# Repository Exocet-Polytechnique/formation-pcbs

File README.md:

# Formation PCBs

Bienvenue à la formation d'Exocet sur la conception de circuits imprimés à l'aide du logiciel
KiCad! Les instructions sous forme écrite sont disponibles sur le
[wiki](https://github.com/Exocet-Polytechnique/formation-pcbs/wiki). Autrement, les quatre parties
de la formation sont dispensées en ligne sur Discord. Les enregistrements sont aussi disponibles à
la demande.

Pour suivre la formation, vous pouvez créer une nouvelle branche sur ce dépôt et la nommer avec
votre nom en minuscules. De cette manière, nous pourrons la visiter pour donner du feedback sur
votre projet.

# Licence

Les instructions sont disponibles publiquement sous la licence `CC0 1.0`, dont le texte est
[disponible ici](LICENSE). Les licences des projets KiCad sont à la discrétion de leurs
contributeurs respectifs. Ainsi, vous n'avez aucun droit sur les fichiers de projet à moins d'en
avoir l'accord explicite de la part du ou des contributeur(s) ayant travaillé dessus.

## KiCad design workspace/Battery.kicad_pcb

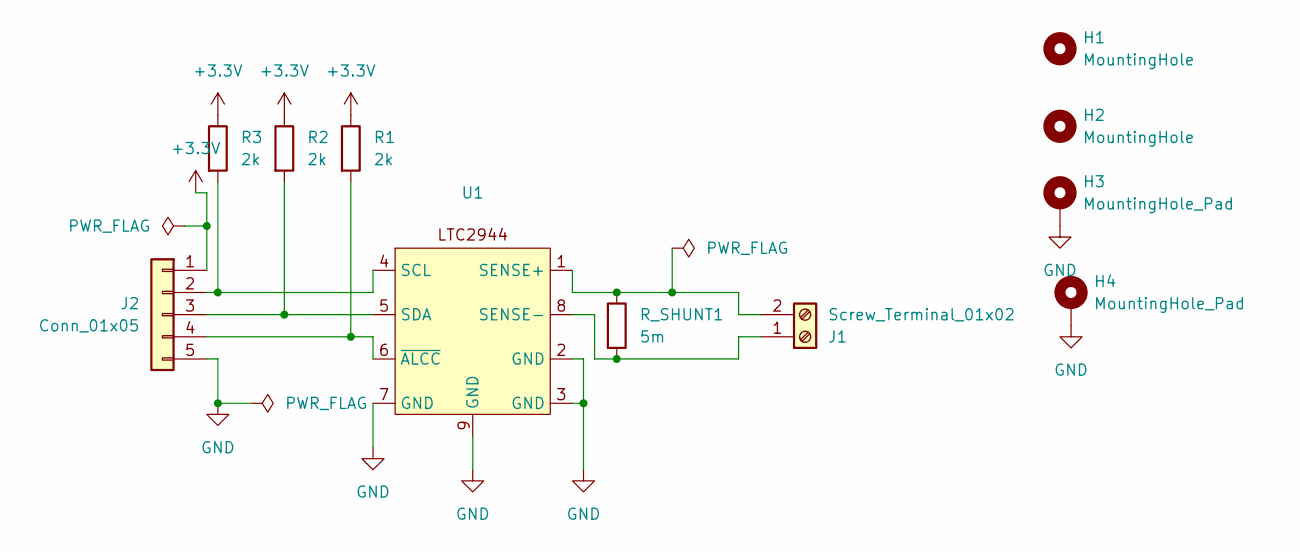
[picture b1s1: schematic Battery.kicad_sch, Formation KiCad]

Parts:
H1, H2: MountingHole; MountingHole_2.7mm
H3, H4: MountingHole_Pad; MountingHole_2.7mm_Pad
J1: Screw_Terminal_01x02; TerminalBlock_Phoenix_MKDS-1,5-2_1x02_P5.00mm_Horizontal
J2: Conn_01x05; JST_PH_S5B-PH-K_1x05_P2.00mm_Horizontal
R1, R2, R3: 2k; R_0603_1608Metric
R_SHUNT1: 5m; Milliohm_Shunt_2512
U1: DFN-8-1EP_3x3mm_P0.5mm_EP1.65x2.38mm_ThermalVias

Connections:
+3.3V: J2.1, R1.1, R2.1, R3.1
GND: H3.1, H4.1, J2.5, U1.2 (GND), U1.3 (GND), U1.7 (GND), U1.9 (GND)
unnamed: J1.1, R_SHUNT1.2, U1.8 (SENSE-)
unnamed: J1.2, R_SHUNT1.1, U1.1 (SENSE+)
unnamed: J2.2, R3.2, U1.4 (SCL)
unnamed: J2.3, R2.2, U1.5 (SDA)
unnamed: J2.4, R1.2, U1.6 (~ALCC)

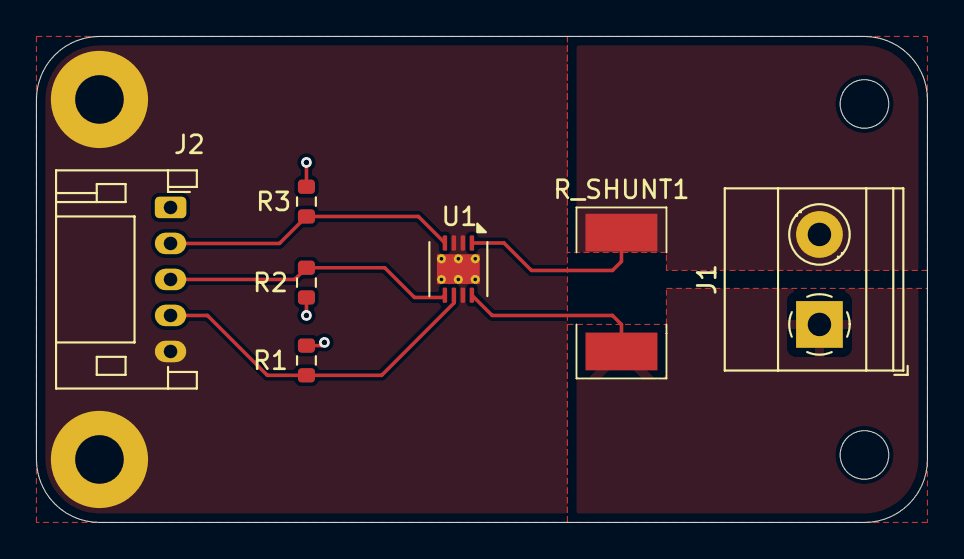
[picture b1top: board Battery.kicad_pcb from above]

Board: 2 copper layers, 49.5 x 27.0 mm, 11 parts (0 on the bottom side), 7 nets.

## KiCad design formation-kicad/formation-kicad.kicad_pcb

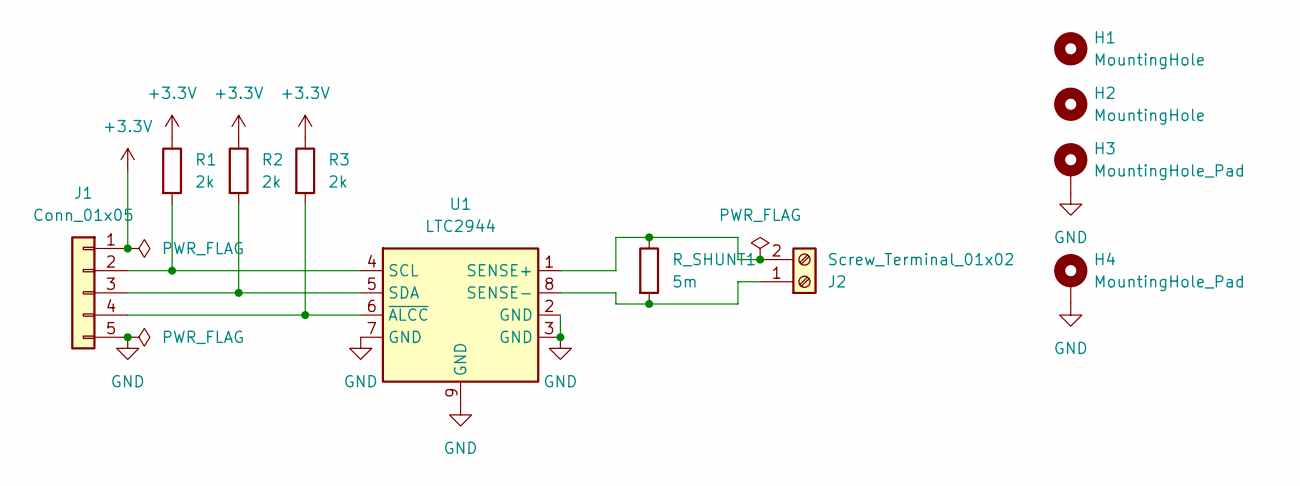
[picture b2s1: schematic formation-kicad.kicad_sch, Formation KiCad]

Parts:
H1, H2: MountingHole; MountingHole_2.7mm
H3, H4: MountingHole_Pad; MountingHole_2.7mm_M2.5_Pad
J1: Conn_01x05; JST_PH_S5B-PH-K_1x05_P2.00mm_Horizontal
J2: Screw_Terminal_01x02; TerminalBlock_Phoenix_MKDS-1,5-2_1x02_P5.00mm_Horizontal
R1, R2, R3: 2k; R_0603_1608Metric
R_SHUNT1: 5m; Milliohm_Shunt_2512
U1: LTC2944; DFN-8-1EP_3x3mm_P0.5mm_EP1.65x2.38mm_ThermalVias

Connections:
+3.3V: J1.1, R1.1, R2.1, R3.1
GND: H3.1, H4.1, J1.5, U1.2 (GND), U1.3 (GND), U1.7 (GND), U1.9 (GND)
unnamed: J1.2, R1.2, U1.4 (SCL)
unnamed: J1.3, R2.2, U1.5 (SDA)
unnamed: J1.4, R3.2, U1.6 (~ALCC)
unnamed: J2.1, R_SHUNT1.2, U1.8 (SENSE-)
unnamed: J2.2, R_SHUNT1.1, U1.1 (SENSE+)

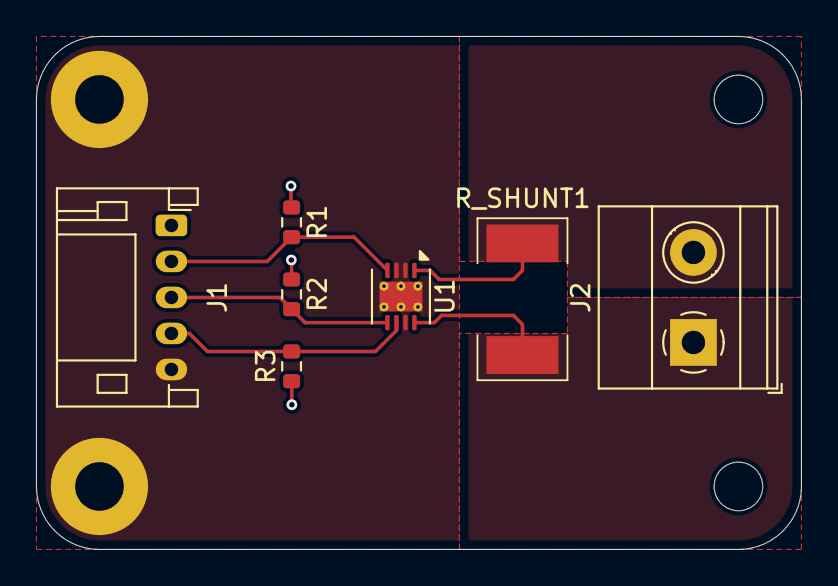
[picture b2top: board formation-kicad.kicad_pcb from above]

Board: 2 copper layers, 42.5 x 28.5 mm, 11 parts (0 on the bottom side), 7 nets.

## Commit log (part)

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2024-09-21 Accueil (README.md)
2024-09-25 Vocabulaire et Introduction
2024-09-26 Compléter l'introduction
2024-09-27 Correction
2024-09-27 Update Vocabulaire.md
    description via
2024-09-27 Update Vocabulaire.md
    correction description via
2024-09-27 Update Vocabulaire.md
    description plan (plane)
2024-09-27 Update Vocabulaire.md
    correction description plan (plane)
2024-09-27 Update Vocabulaire.md
    description empreinte
2024-09-29 Update Vocabulaire.md
    Ajouté quelques descriptions supplémentaires aux pièces et aux planes
2024-09-29 Add files via upload
    Ajout d'images pertinentes
2024-09-29 Rename image.png to Transistor.png
2024-09-29 Update 0. Introduction.md
    me souviens plus ce que j'ai fait
2024-09-29 Update 1. Introduction.md
    Ajout de certaines étapes pertinentes à la réalisation d'un PCB
2024-09-29 Update Vocabulaire.md
    Images
2024-09-29 ajout images
    duh
2024-09-29 Rename Screenshot from 2024-09-29 03-52-46.png to Decouplage
2024-09-29 creation projet kicad
2024-10-04 Begin schematics instructions
2024-10-04 Move to Wiki
2024-10-04 Proofread README
2024-10-04 Notify main branch update
2024-10-05 Add KiCad temporary files to gitignore
2024-10-13 commit1
2024-10-13 formation 2
2024-10-13 symbol placement
2024-10-17 formation 3
2024-11-06 Partie 1 à 3 des formations
2024-11-11 Formation 3/4
